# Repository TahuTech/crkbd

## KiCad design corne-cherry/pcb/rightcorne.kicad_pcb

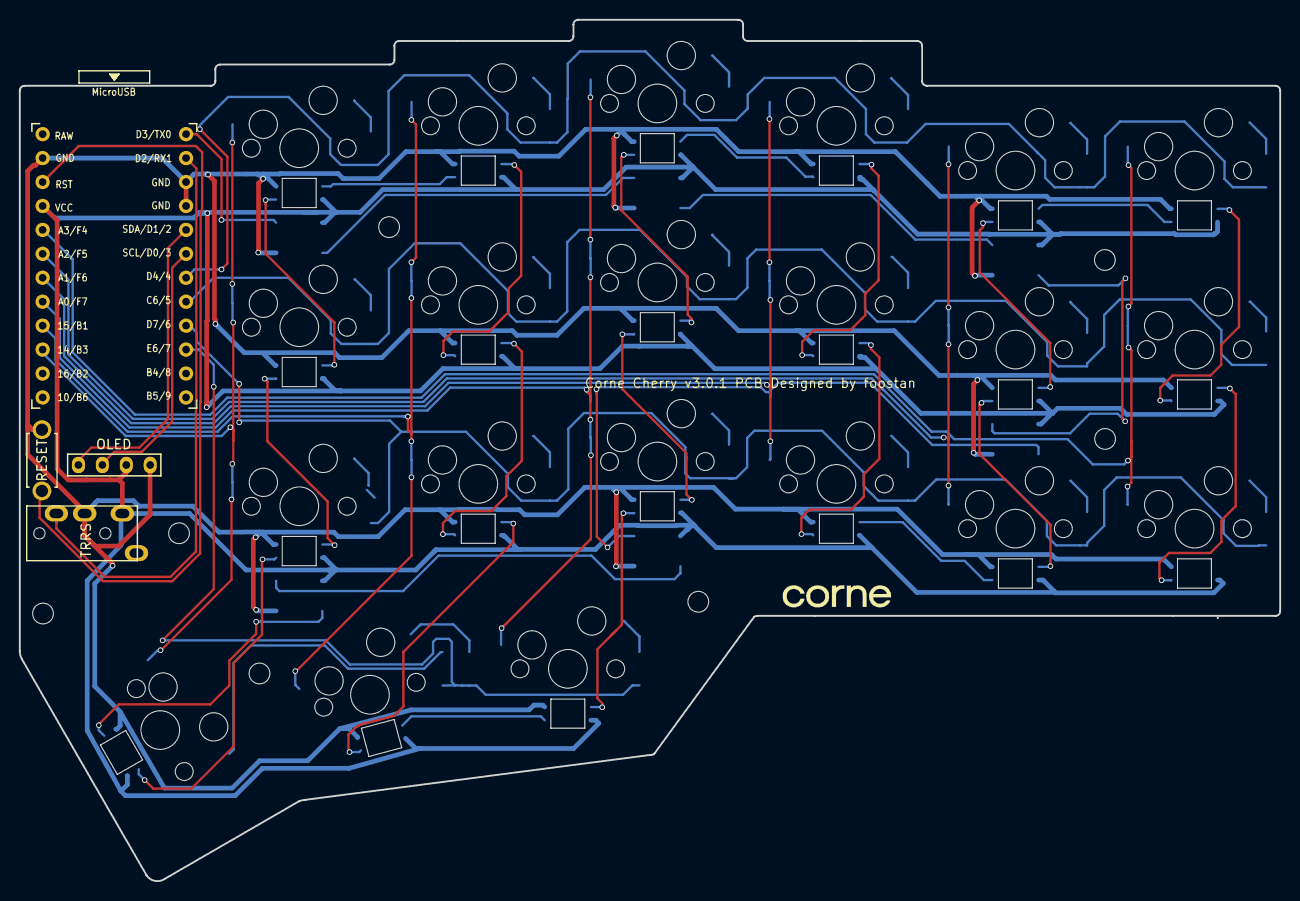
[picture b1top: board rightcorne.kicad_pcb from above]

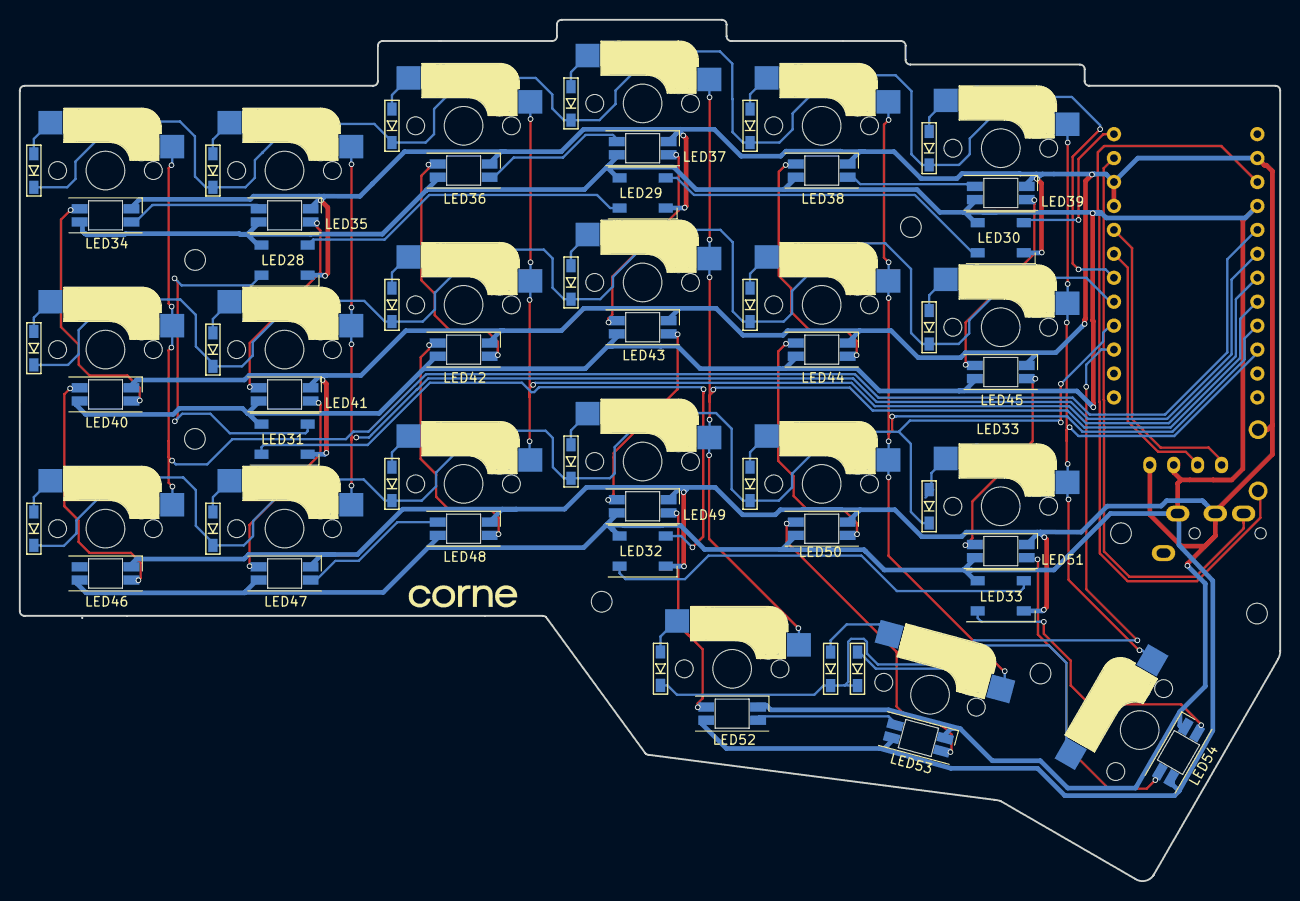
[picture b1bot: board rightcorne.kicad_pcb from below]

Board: 2 copper layers, 133.8 x 91.4 mm, 80 parts (51 on the bottom side), 64 nets.

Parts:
D22, D23, D24, D25, D26, D27, D28, D29, D30, D31, D32, D33, D34, D35, D36, D37, D38, D39, D40, D41, D42: D; D3_SMD_v2
J3: MJ-4PP-9; MJ-4PP-9_1side
J4: OLED; OLED_1side
LED28, LED29, LED30, LED31, LED32, LED33: WS2812B; LED_WS2812B_PLCC4_5.0x5.0mm_P3.2mm
LED34, LED35, LED36, LED37, LED38, LED39, LED40, LED41, LED42, LED43, LED44, LED45, LED46, LED47, LED48, LED49, LED50, LED51, LED52, LED53, LED54: YS-SK6812MINI-E
RSW2: SW_PUSH; ResetSW_1side
Ref**: Val**; MountingHole_2.2mm_M2
Ref**#2, Ref**#3, Ref**#4, Ref**#5, Ref**#6, Ref**#7: Val**; MountingHole_2.2mm_M2
SW22, SW23, SW24, SW25, SW26, SW27, SW28, SW29, SW30, SW31, SW32, SW33, SW34, SW35, SW36, SW37, SW38, SW39, SW40, SW41: SW_PUSH; CherryMX_Hotswap
SW42: SW_PUSH; CherryMX_Hotswap_1.5u
U2: ProMicro; ProMicro_v3

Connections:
GNDA: J3.C, J4.4, LED28.3, LED29.3, LED30.3, LED31.3, LED32.3, LED33.3, LED34.3, LED35.3, LED36.3, LED37.3, LED38.3, LED39.3, LED40.3, LED41.3, LED42.3, LED43.3, LED44.3, LED45.3, LED46.3, LED47.3, LED48.3, LED49.3, LED50.3, LED51.3, LED52.3, LED53.3, LED54.3, RSW2.2, U2.3, U2.4, U2.23
LED_r: LED30.4, U2.1
unnamed: D22.2, SW22.2
unnamed: D23.2, SW23.2
unnamed: D24.2, SW24.2
unnamed: D25.2, SW25.2
unnamed: D26.2, SW26.2
unnamed: D27.2, SW27.2
unnamed: D28.2, SW28.2
unnamed: D29.2, SW29.2
unnamed: D30.2, SW30.2
unnamed: D31.2, SW31.2
unnamed: D32.2, SW32.2
unnamed: D33.2, SW33.2
unnamed: D34.2, SW34.2
unnamed: D35.2, SW35.2
unnamed: D36.2, SW36.2
unnamed: D37.2, SW37.2
unnamed: D38.2, SW38.2
unnamed: D39.2, SW39.2
unnamed: D40.2, SW40.2
unnamed: D41.2, SW41.2
unnamed: D42.2, SW42.2
unnamed: LED28.2, LED31.4
unnamed: LED28.4, LED29.2
unnamed: LED29.4, LED30.2
unnamed: LED31.2, LED32.4
unnamed: LED32.2, LED33.4
unnamed: LED33.2, LED54.4
unnamed: LED34.2, LED40.4
unnamed: LED34.4, LED35.2
unnamed: LED35.4, LED41.2
unnamed: LED36.2, LED42.4
unnamed: LED36.4, LED37.2
unnamed: LED37.4, LED43.2
unnamed: LED38.2, LED44.4
unnamed: LED38.4, LED39.2
unnamed: LED39.4, LED45.2
unnamed: LED40.2, LED46.4
unnamed: LED41.4, LED47.2
unnamed: LED42.2, LED48.4
unnamed: LED43.4, LED49.2
unnamed: LED44.2, LED50.4
unnamed: LED45.4, LED51.2
unnamed: LED47.4, LED48.2
unnamed: LED49.4, LED52.2
unnamed: LED50.2, LED53.4
unnamed: LED51.4, LED54.2
unnamed: LED52.4, LED53.2
SCL_r: J4.2, U2.6
SDA_r: J4.1, U2.5
VDD: J3.D, J4.3, LED28.1, LED29.1, LED30.1, LED31.1, LED32.1, LED33.1, LED34.1, LED35.1, LED36.1, LED37.1, LED38.1, LED39.1, LED40.1, LED41.1, LED42.1, LED43.1, LED44.1, LED45.1, LED46.1, LED47.1, LED48.1, LED49.1, LED50.1, LED51.1, LED52.1, LED53.1, LED54.1, U2.21
col0_r: SW22.1, SW28.1, SW34.1, U2.20
col1_r: SW23.1, SW29.1, SW35.1, U2.19
col2_r: SW24.1, SW30.1, SW36.1, U2.18
col3_r: SW25.1, SW31.1, SW37.1, SW40.1, U2.17
col4_r: SW26.1, SW32.1, SW38.1, SW41.1, U2.16
col5_r: SW27.1, SW33.1, SW39.1, SW42.1, U2.15
data_r: J3.B, U2.2
reset_r: RSW2.1, U2.22
row0_r: D22.1, D23.1, D24.1, D25.1, D26.1, D27.1, U2.7
row1_r: D28.1, D29.1, D30.1, D31.1, D32.1, D33.1, U2.8
row2_r: D34.1, D35.1, D36.1, D37.1, D38.1, D39.1, U2.9
row3_r: D40.1, D41.1, D42.1, U2.10

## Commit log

2021-12-08 modified corne-cherry pcb
2021-12-08 add acrylic case and plates
